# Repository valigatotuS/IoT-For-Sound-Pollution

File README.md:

# IoT-For-Sound-Pollution

IoT and LoRaWAN for sound pollution

## Project Description

This is part of a bachelor-thesis in Industrial Engineering [3BA, ELO-ICT]

## Deploy project

- Get pycom's FiPy/LoPy4, a pygate shield and antenna's
- Upload the respective folders to the devices (src/IoT-devices/...)
- Configure the Network-Server (in this case TheThingsNetwork)

## Credits

- Abdellah Touhafi

### Sources

- https://github.com/pycom/pycom-libraries

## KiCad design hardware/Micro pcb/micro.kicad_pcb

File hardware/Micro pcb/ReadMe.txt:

This file contains several things:
	- KiCad project containing all
	- schematics ...(explain components)
	- pcb design ...(explain pcb parameters)
	- parts: ICS-403000(microphone) and OPA344UA(single rail OPAMP) ... (short explaination why these components)

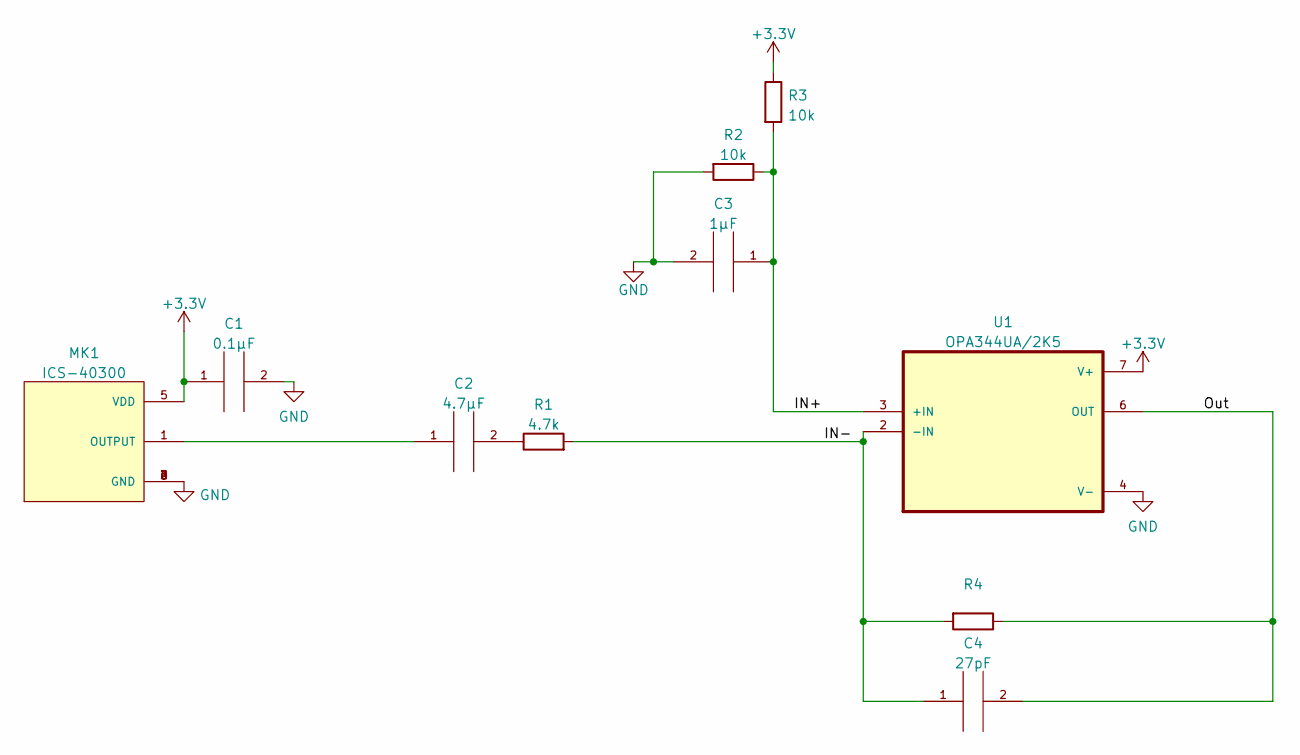
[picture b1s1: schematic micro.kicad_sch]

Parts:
C1: 0.1µF; C_0201_0603Metric_Pad0.64x0.40mm_HandSolder
C2: 4.7µF; C_0201_0603Metric_Pad0.64x0.40mm_HandSolder
C3: 1µF; C_0201_0603Metric_Pad0.64x0.40mm_HandSolder
C4: 27pF; C_0201_0603Metric_Pad0.64x0.40mm_HandSolder
MK1: ICS-40300; MIC_ICS-40300
R1: 4.7k; R_1206_3216Metric_Pad1.30x1.75mm_HandSolder
R2, R3: 10k; R_1206_3216Metric_Pad1.30x1.75mm_HandSolder
R4: R_1206_3216Metric_Pad1.30x1.75mm_HandSolder
U1: OPA344UA/2K5; SOIC127P599X175-8N

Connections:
+3V3: C1.1, MK1.5 (VDD), R3.1, U1.7 (V+)
/IN+: C3.1, R2.1, R3.2, U1.3 (+IN)
/IN-: C4.1, R1.2, R4.2, U1.2 (-IN)
/Out: C4.2, R4.1, U1.6 (OUT)
GND: C1.2, C3.2, MK1.2 (GND), MK1.3 (GND), MK1.4 (GND), MK1.6 (GND), R2.2, U1.4 (V-)
unnamed: C2.1, MK1.1 (OUTPUT)
unnamed: C2.2, R1.1

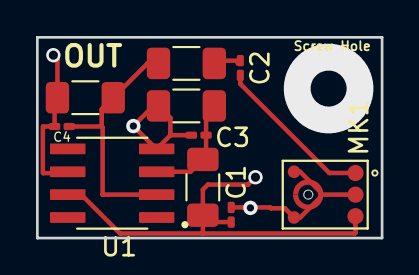
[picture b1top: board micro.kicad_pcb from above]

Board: 2 copper layers, 19.2 x 11.2 mm, 10 parts (0 on the bottom side), 7 nets.

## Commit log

2022-02-18 init repo
2022-02-18 test commit
2022-02-18 remove test commit
2022-02-18 add .gitignore
2022-02-18 add test code for µc
2022-02-19 add test code for Pycom µc
2022-03-17 add gateway & node base code
2022-03-17 restructure folder
2022-03-17 add chirpstack server
2022-03-17 update structure
2022-03-17 add doc
2022-04-09 update OTAA mode (working)
2022-04-09 update otaa node (2)
2022-04-10 update otaa node (3)
2022-04-10 update otaa node (4)
    uplink & downlink working
2022-04-14 update otaa node (4)
    add send_sound()
2022-04-14 add tig-stack
    working grafana with dummy sensor data
2022-04-14 add global working noisenode
2022-04-15 Adding ReadMe
2022-04-17 update NoiseNose
    working : uplink/downlink with 60% succes-rate of tranmission
2022-04-17 add tick-stack
2022-04-18 add simulation 3
2022-04-23 update node
2022-05-01 update iot devs
2022-05-01 add gnu radio for freq analysis
2022-05-01 add tig stack
2022-05-08 update single gateway
2022-05-08 add multi gateway
2022-05-08 add gnu tests
2022-05-19 update IoT devices
2022-05-23 final patch
2022-08-27 add documentation
2022-08-27 add random-channel hopping feature
